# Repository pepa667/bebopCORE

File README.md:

# bebopCORE

Firmware para ESP32 destinado à criação de gamepads Bluetooth compatíveis com Nintendo Switch e dispositivos HID.
ESP32 firmware for creating Bluetooth gamepads compatible with Nintendo Switch and HID devices.

## 🕹️ Inputs

- D-Pad (Up, Down, Left, Right)
- Buttons A & B
- Start & Select
- L & R
- 4 Fn Keys

## 🛠️ Dependências e Créditos / Dependencies and Credits

Este projeto é desenvolvido utilizando as seguintes bibliotecas e repositórios como base:
This project is developed using the following libraries and repositories as a base:

- [BluN64-ESP32](https://github.com/JPZV/BluN64-ESP32)
- [BluControl-SDK-ESP32](https://github.com/JPZV/BluControl-SDK-ESP32)
- [HOJA-LIB-ESP32](https://github.com/HandHeldLegend/HOJA-LIB-ESP32)

## 📄 Licença / License

Este projeto segue a licença **Creative Commons Attribution-NonCommercial-ShareAlike 4.0 International (CC BY-NC-SA 4.0)**, acompanhando as permissões e restrições das fontes utilizadas.

This project follows the **Creative Commons Attribution-NonCommercial-ShareAlike 4.0 International (CC BY-NC-SA 4.0)** license, in accordance with the permissions and restrictions of the source materials used.

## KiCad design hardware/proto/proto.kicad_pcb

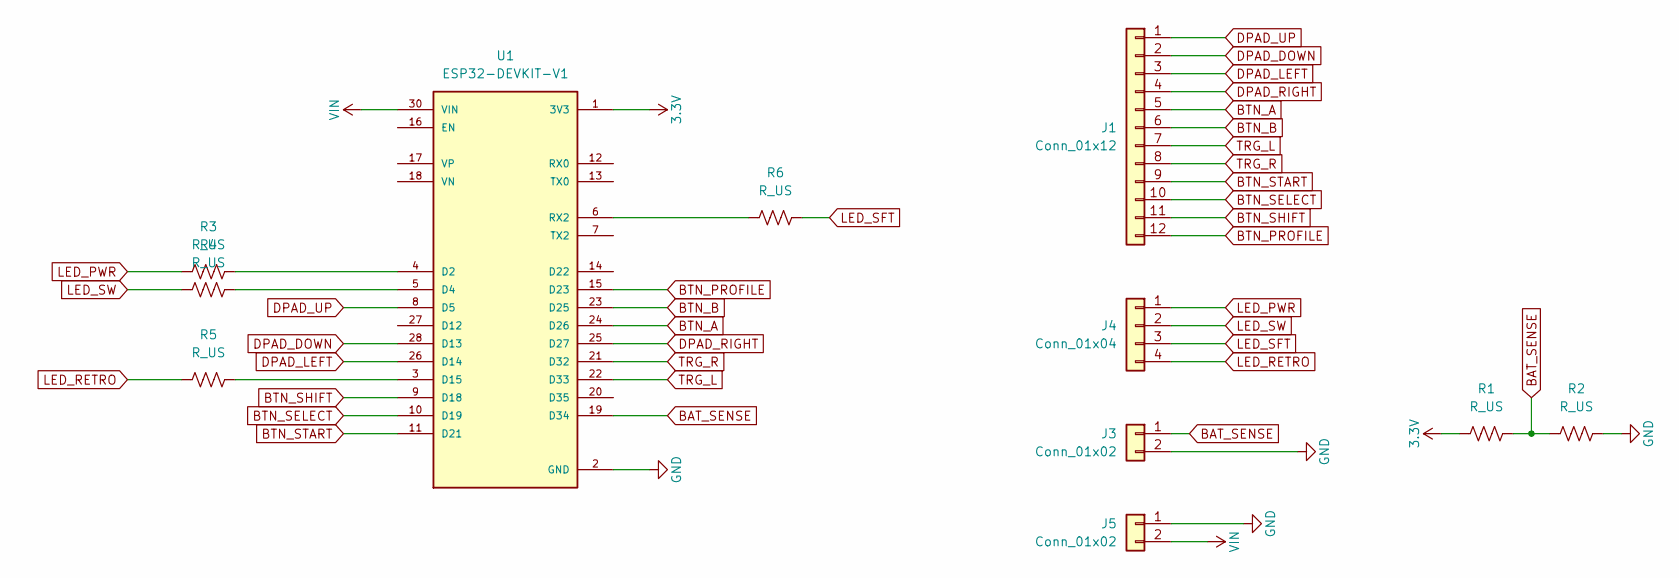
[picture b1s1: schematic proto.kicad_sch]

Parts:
J1: Conn_01x12; PhoenixContact_MCV_1,5_12-G-5.08_1x12_P5.08mm_Vertical
J3, J5: Conn_01x02; SolderWire-1sqmm_1x02_P5.4mm_D1.4mm_OD2.7mm
J4: Conn_01x04; SolderWire-1sqmm_1x04_P5.4mm_D1.4mm_OD2.7mm
R1, R2, R3, R4, R5, R6: R_US; R_Axial_DIN0204_L3.6mm_D1.6mm_P10.16mm_Horizontal
U1: ESP32-DEVKIT-V1; MODULE_ESP32_DEVKIT_V1; PARTREV N/A

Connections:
3.3V: R1.1, U1.1 (3V3)
BAT_SENSE: J3.1, R1.2, R2.1, U1.19 (D34)
BTN_A: J1.5, U1.24 (D26)
BTN_B: J1.6, U1.23 (D25)
BTN_PROFILE: J1.12, U1.15 (D23)
BTN_SELECT: J1.10, U1.10 (D19)
BTN_SHIFT: J1.11, U1.9 (D18)
BTN_START: J1.9, U1.11 (D21)
DPAD_DOWN: J1.2, U1.28 (D13)
DPAD_LEFT: J1.3, U1.26 (D14)
DPAD_RIGHT: J1.4, U1.25 (D27)
DPAD_UP: J1.1, U1.8 (D5)
GND: J3.2, J5.1, R2.2, U1.2 (GND), U1.29 (GND)
LED_PWR: J4.1, R3.1
LED_RETRO: J4.4, R5.1
LED_SFT: J4.3, R6.2
LED_SW: J4.2, R4.1
unnamed: R3.2, U1.4 (D2)
unnamed: R4.2, U1.5 (D4)
unnamed: R5.2, U1.3 (D15)
unnamed: R6.1, U1.6 (RX2)
TRG_L: J1.7, U1.22 (D33)
TRG_R: J1.8, U1.21 (D32)
VIN: J5.2, U1.30 (VIN)

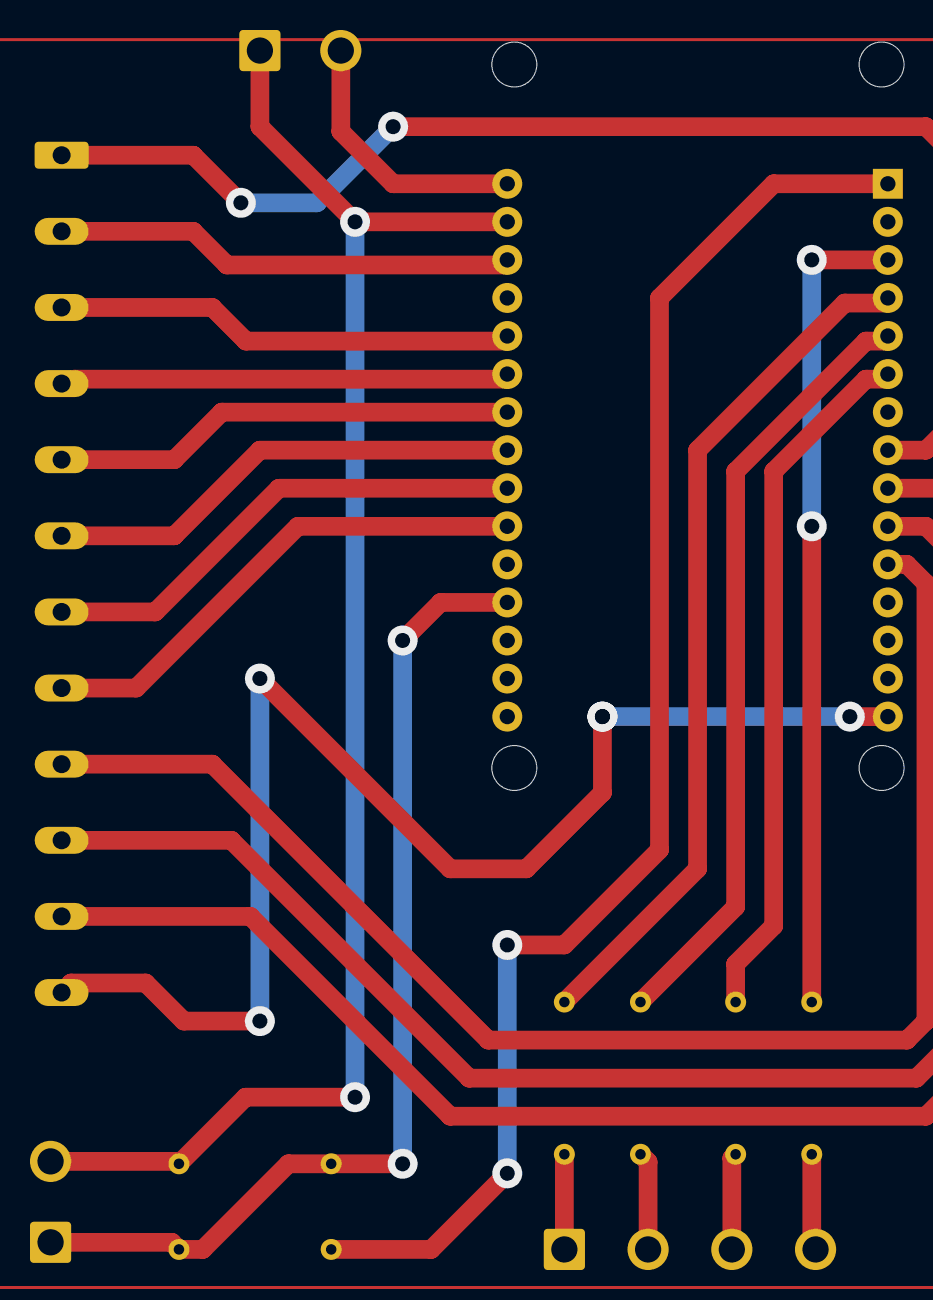
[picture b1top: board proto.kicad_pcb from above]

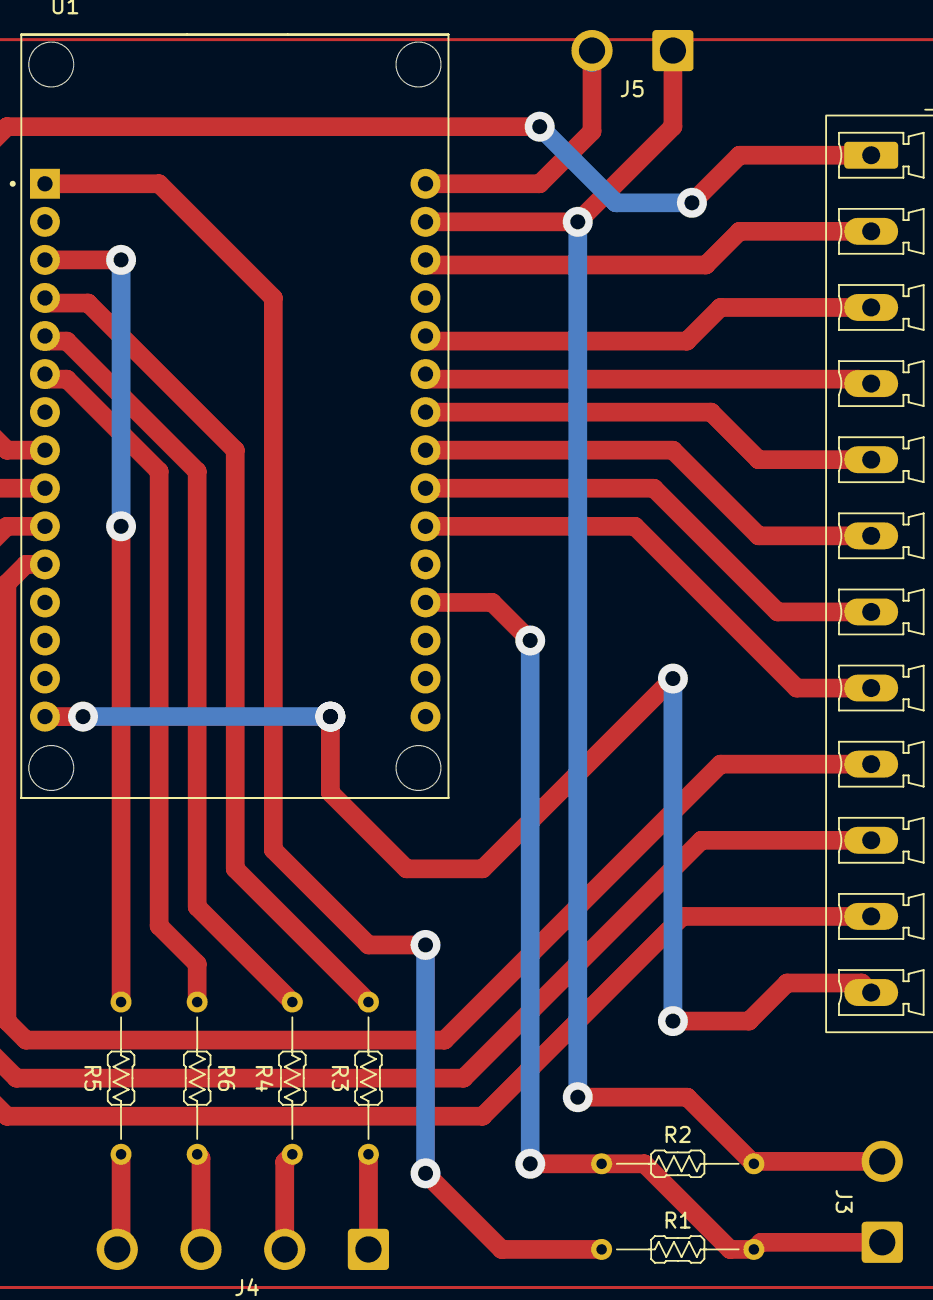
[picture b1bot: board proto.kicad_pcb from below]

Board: 2 copper layers, 11 parts (11 on the bottom side), 24 nets.

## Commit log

2026-04-11 Translate README.md to English
    Translated README content from Portuguese to English.
2026-04-11 Starting SubModules
2026-04-11 First Build – Testing
2026-04-11 FOOOOORKS
2026-04-11 Clean Reset
2026-04-11 First Build
2026-04-12 Adicionado script shell para agilizar os commits
2026-04-17 1st Build
2026-04-17 Rebrand
2026-04-17 Change submodule branch from 'main' to 'brand'
2026-04-24 Keeping it clean
2026-04-25 Começãdo a prototipar o hardware do Bebop, e fazendo algumas mudanças no código para suportar o novo hardware. Ainda não tem nada funcional, mas é um começo!
2026-04-25 Restarting
2026-04-25 Removed submodule <name>
2026-04-25 Fresh Start
2026-04-25 Tô quase chorando!!!
2026-05-01 Funciona! Só que não (˃̣̣̥ᯅ˂̣̣̥)
2026-05-09 Prototype hardware for testing and more
2026-05-10 Tudo cagado...
2026-05-10 cagado
2026-05-16 Um dia eu arrumo tudo
2026-05-16 Tentando algo novo
2026-05-16 Nem me pergunta o que eu to fazendo que nem eu faço ideia
2026-05-16 pra não perder tudo, de novo
